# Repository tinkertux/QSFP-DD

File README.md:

# QSFP-DD
REV A for code EEPROM

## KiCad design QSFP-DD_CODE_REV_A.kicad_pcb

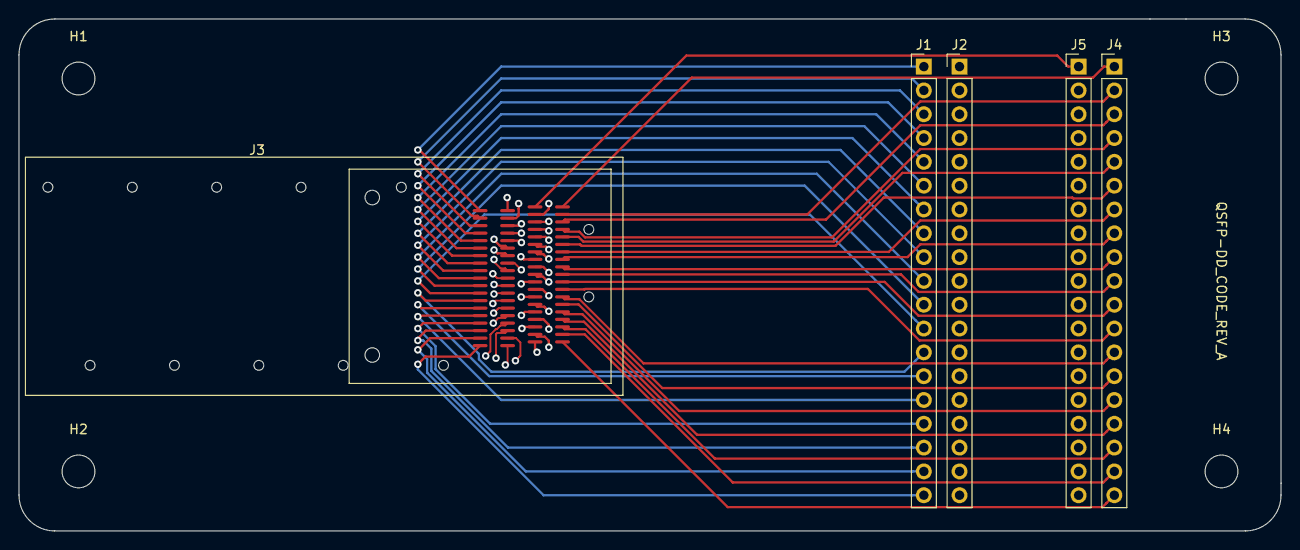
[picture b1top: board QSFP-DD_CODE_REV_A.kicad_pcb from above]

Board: 4 copper layers, 134.6 x 54.6 mm, 9 parts (0 on the bottom side), 76 nets.

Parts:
H1, H2, H3, H4: MountingHole; MountingHole_3.5mm
J1, J2, J4, J5: Conn_01x19_Male; PinHeader_1x19_P2.54mm_Vertical
J3: QSFP-DD_F

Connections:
/InitMode: J3.31, J4.8
/IntL: J3.28, J4.11
/ModPrsL: J3.27, J4.12
/ModselL: J1.8, J3.8
/RX1n: J1.18, J3.18
/RX1p: J1.17, J3.17
/RX2n: J3.21, J4.18
/RX2p: J3.22, J4.17
/RX3n: J1.15, J3.15
/RX3p: J1.14, J3.14
/RX4n: J3.24, J4.15
/RX4p: J3.25, J4.14
/RX5n: J2.18, J3.56
/RX5p: J2.17, J3.55
/RX6n: J3.59, J5.18
/RX6p: J3.60, J5.17
/RX7n: J2.15, J3.53
/RX7p: J2.14, J3.52
/RX8n: J3.62, J5.15
/RX8p: J3.63, J5.14
/ResetL: J1.9, J3.9
/SCL: J1.11, J3.11
/SDA: J1.12, J3.12
/TX1n: J3.37, J4.2
/TX1p: J3.36, J4.3
/TX2n: J1.2, J3.2
/TX2p: J1.3, J3.3
/TX3n: J3.34, J4.5
/TX3p: J3.33, J4.6
/TX4n: J1.5, J3.5
/TX4p: J1.6, J3.6
/TX5n: J3.75, J5.2
/TX5p: J3.74, J5.3
/TX6n: J2.2, J3.40
/TX6p: J2.3, J3.41
/TX7n: J3.72, J5.5
/TX7p: J3.71, J5.6
/TX8n: J2.5, J3.43
/TX8p: J2.6, J3.44
/VS1: J2.9, J3.47
/VS2: J2.11, J3.49
/VS3: J2.12, J3.50
/Vcc1: J3.30, J4.9
/Vcc2: J3.68, J5.9
/VccRx: J1.10, J3.10
/VccRx1: J2.10, J3.48
/VccTx: J3.29, J4.10
/VccTx1: J3.67, J5.10
unnamed: J1.1, J3.1
unnamed: J1.4, J3.4
unnamed: J1.7, J3.7
unnamed: J1.13, J3.13
unnamed: J1.16, J3.16
unnamed: J1.19, J3.19
unnamed: J2.1, J3.39
unnamed: J2.4, J3.42
unnamed: J2.7, J3.45
unnamed: J2.8, J3.46
unnamed: J2.13, J3.51
unnamed: J2.16, J3.54
unnamed: J2.19, J3.57
unnamed: J3.20, J4.19
unnamed: J3.23, J4.16
unnamed: J3.26, J4.13
unnamed: J3.32, J4.7
unnamed: J3.35, J4.4
unnamed: J3.38, J4.1
unnamed: J3.58, J5.19
unnamed: J3.61, J5.16
unnamed: J3.64, J5.13
unnamed: J3.65, J5.12
unnamed: J3.66, J5.11
unnamed: J3.69, J5.8
unnamed: J3.70, J5.7
unnamed: J3.73, J5.4
unnamed: J3.76, J5.1

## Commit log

2020-02-11 add project file
2020-02-11 add schematic file
2020-02-11 add pcb file
2020-02-11 Initial version
